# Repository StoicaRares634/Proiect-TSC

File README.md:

# Proiect-TSC
Proiect-TSC Stoica Rares-Nicolae 333CA

| Device                                                                       | CHECK_PRICES                                                                                                                                                     |
|------------------------------------------------------------------------------|------------------------------------------------------------------------------------------------------------------------------------------------------------------|
| ESP32_WROVER_EAGLE-LTSPICE_CC0402                                            |                                                                                                                                                                  |
| RCL_CPOL-EUCT3528                                                            | https://a360.co/4iZy6AA                                                                                                                                           |
| CPH3225A                                                                     | https://www.snapeda.com/parts/CPH3225A/Seiko+Instruments/view-part/?ref=eda                                                                                       |
| BUTTON_CUSYOMV1                                                              | https://industry.panasonic.com/global/en/products/control/switch/light-touch/number/evqpuj02k                                                                     |
| ADAFRUIT_LEDCHIP-LED0603                                                     | https://www.snapeda.com/parts/KP-1608SURCK/Kingbright/view-part/?ref=search                                                                                       |
| USBLC6-2SC6Y                                                                 | https://www.snapeda.com/parts/USBLC6-2SC6Y/STMicroelectronics/view-part/?ref=eda                                                                                  |
| ESP32_WROVER_AVX---SD0805S020S1R0                                            | https://eu.mouser.com/ProductDetail/KYOCERA-AVX/SD0805S020S1R0?qs=jCA%252BPfw4LHbpkAoSnwrdjw%3D%3D                                                                |
| MBR0530                                                                      | https://www.snapeda.com/parts/MBR0530/Onsemi/view-part/?ref=eda                                                                                                   |
| PGB1010603MR                                                                 | https://www.snapeda.com/parts/PGB1010603MR/Littelfuse/view-part/?ref=eda                                                                                          |
| BD5229G-TR                                                                   | https://componentsearchengine.com/part-view/BD5229G-TR/ROHM%20Semiconductor                                                                                       |
| XC6220A331MR-G                                                               | https://componentsearchengine.com/part-view/XC6220A331MR-G/Torex                                                                                                  |
| FH34SRJ-24S-0.5SH_99_                                                        | https://componentsearchengine.com/part-view/XC6220A331MR-G/Torex                                                                                                  |
| SAMACSYS_PARTS_USB4110-GF-A                                                  | https://componentsearchengine.com/part-view/USB4110-GF-A/GCT%20(GLOBAL%20CONNECTOR%20TECHNOLOGY)                                                                  |
| 112A-TAAR-R03_ATTEND                                                         | https://store.comet.srl.ro/Catalogue/Product/43497/                                                                                                               |
| 744043680IND_4828-WE-TPC_WRE                                                 | https://eu.mouser.com/ProductDetail/Wurth-Elektronik/744043680?qs=PGXP4M47uW6VkZq%252BkzjrHA%3D%3D                                                                |
| ESP32C6_VARISTORCN1812                                                       | https://www.mouser.co.uk/ProductDetail/EPCOS-TDK/B72520T0350K062?qs=dEfas%2FXlABIszF52uu7vrg%3D%3D                                                                |
| ESP32_WROVER_SPARKFUN-DISCRETESEMI_MOSFET_PCH-DMG2305UX-7                    | https://componentsearchengine.com/part-view/DMG2305UX-7/Diodes%20Incorporated                                                                                     |
| D8                                                                           | https://componentsearchengine.com/part-view/SI1308EDL-T1-GE3/Vishay                                                                                               |
| ESP32_WROVER_EAGLE-LTSPICE_RR0402                                            | https://componentsearchengine.com/part-view/R0402%201%25%20100%20K%20(RC0402FR-07100KL)/YAGEO                                                                     |
| BME680                                                                       | https://www.snapeda.com/parts/BME680/Bosch/view-part/?welcome=home                                                                                                |
| SJ                                                                           | https://grabcad.com/library/solder-jumpers-1                                                                                                                     |
| W25Q512JVEIQ                                                                 | https://www.snapeda.com/parts/W25Q512JVEIQ/Winbond+Electronics/view-part/?ref=eda                                                                                 |
| ESP32-C6-WROOM-1-N8                                                          | https://www.snapeda.com/parts/ESP32-C6-WROOM-1-N8/Espressif+Systems/view-part/?ref=eda                                                                            |
| DS3231SN#                                                                    | https://www.snapeda.com/parts/DS3231SN%23/Analog+Devices/view-part/?ref=eda                                                                                       |
| MAX17048G+T10                                                                | https://www.snapeda.com/parts/MAX17048G+T10/Analog+Devices/view-part/?ref=eda                                                                                     |

## Descriere detaliata a functionalitatii hardware

Proiectul utilizeaza microcontroller-ul ESP32-C6 WROOM. Acesta gestioneaza comunicatia cu diverse module prin interfete SPI, I2C si GPIO, avand capacitate extinsa pentru conectivitate wireless si control de periferice.

### Structura de alimentare

- Conector USB-C: asigura alimentarea externa si transferul de date.
- Controler incarcare baterie Li-Po (MCP73831): integreaza functii de incarcare sigura si controlata a bateriei.
- Baterie Li-Po: sursa de energie mobila, folosita pentru autonomie.
- LDO Regulator (XC6206): reduce tensiunea de la baterie la 3.3V stabili, necesari ESP32 si altor componente.

### Module conectate la ESP32-C6 si interfetele lor

#### 1. Senzor ambiental BME688
- Interfata: I2C
- Functii: detecteaza temperatura, presiune, umiditate si compusi volatili (calitate aer).
- Pini ESP32-C6:
  - GPIO4 → SDA
  - GPIO5 → SCL
GPIO4 si GPIO5 sunt GPIO standard cu suport I2C hardware.

#### 2. Modul RTC – DS3231SN
- Interfata: I2C
- Functii: mentine timpul real precis, inclusiv in standby.
- Pini ESP32-C6:
  - Impartiti cu BME688: GPIO4 (SDA) si GPIO5 (SCL)

#### 3. Memorie externa NOR Flash – W25Q512JVEIQ
- Interfata: SPI
- Functii: stocare extensiva de date nevolatile (64MB).
- Pini ESP32-C6:
  - GPIO6 → CLK
  - GPIO7 → MISO
  - GPIO8 → MOSI
  - GPIO9 → CS (Flash)
Aceasta configuratie este conforma cu pinii dedicati SPI al ESP32-C6 pentru performanta maxima.

#### 4. Modul SD Card
- Interfata: SPI (partajata cu NOR Flash)
- Pini ESP32-C6:
  - GPIO10 → CS (SD Card)
Se foloseste acelasi bus SPI ca Flash-ul, dar cu CS separat pentru selectare.

#### 5. E-Paper Display
- Subcomponente:
  - Circuit de tip e-paper + selector de tip ecran
  - Header pentru display
- Interfata: SPI
- Pini ESP32-C6:
  - GPIO11 → CS (E-Paper)
  - GPIO12 → RES (Reset)
  - GPIO13 → BUSY (Stare de incarcare)
GPIO11–13 sunt configurabili si sunt utilizati pentru semnale de control specifice E-Paper.

#### 6. Butoane de control (BOOT, RESET, CHANGE)
- Interfata: GPIO
- Pini ESP32-C6:
  - GPIO0 → BOOT
  - GPIO1 → RESET
  - GPIO2 → CHANGE
- Utilitate: ofera control manual pentru operatii precum boot, test sau configurare.

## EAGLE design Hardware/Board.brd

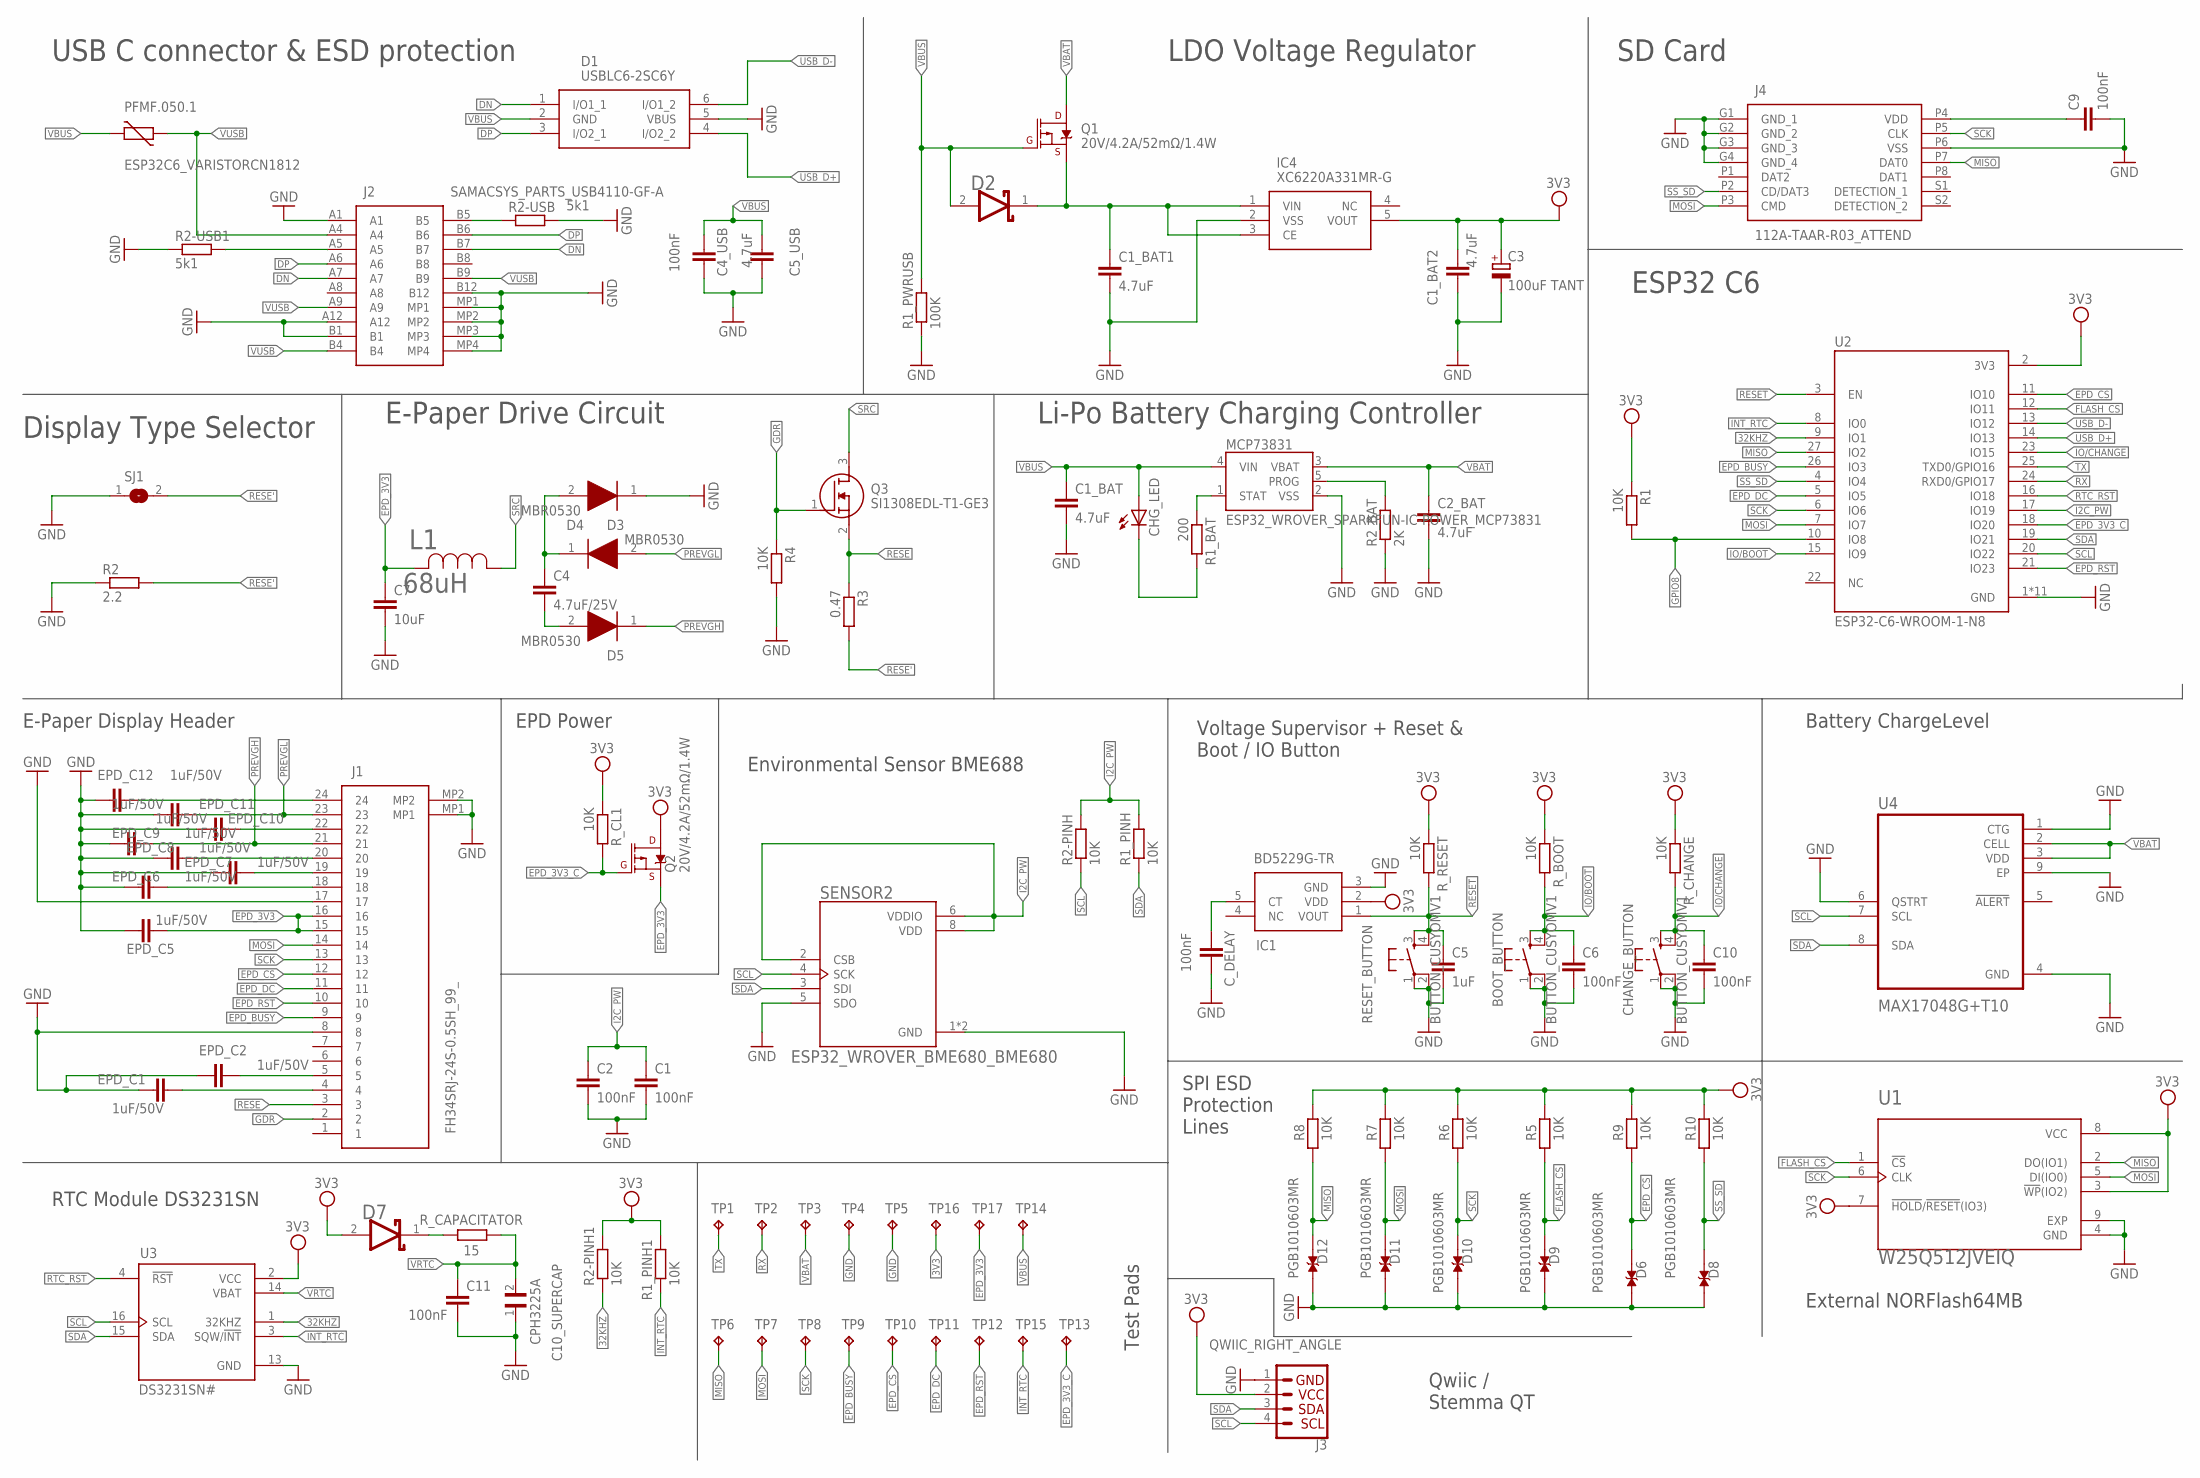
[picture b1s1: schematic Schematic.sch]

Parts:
BOOT_BUTTON: BUTTON_CUSYOMV1; MYBUTTON
C1, C2, C4_USB, C6, C10: 100nF; EAGLE-LTSPICE_C0402
C1_BAT, C1_BAT1, C5_USB: 4.7uF; EAGLE-LTSPICE_C0402
C1_BAT2, C2_BAT: 4.7uF; ESP32_WROVER_EAGLE-LTSPICE_C0402
C3: 100uF TANT; RCL_CT3528
C4: 4.7uF/25V; ESP32_WROVER_EAGLE-LTSPICE_C0402
C5: 1uF; EAGLE-LTSPICE_C0402
C7: 10uF; EAGLE-LTSPICE_C0402
C9, C11: 100nF; ESP32_WROVER_EAGLE-LTSPICE_C0402
C10_SUPERCAP: CPH3225A; CAPCP3225X100N
CHANGE_BUTTON: BUTTON_CUSYOMV1; MYBUTTON
CHG_LED: ADAFRUIT_LEDCHIP-LED0603; ADAFRUIT_CHIP-LED0603
C_DELAY: 100nF; EAGLE-LTSPICE_C0402
D1: USBLC6-2SC6Y; SOT95P280X145-6N
D2, D7: ESP32_WROVER_AVX---SD0805S020S1R0_AVX_SD0805S020S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; ESP32_WROVER_AVX---SD0805S020S1R0_AVX_SD0805S020S1R0_0
D3, D4, D5: MBR0530; SOD3716X135N
D6, D8, D9, D10, D11, D12: PGB1010603MR; DIOC1608X36N
EPD_C1, EPD_C2, EPD_C5, EPD_C6, EPD_C7, EPD_C8, EPD_C9, EPD_C10, EPD_C11, EPD_C12: 1uF/50V; EAGLE-LTSPICE_C0402
IC1: BD5229G-TR; SOT95P280X125-5N
IC4: XC6220A331MR-G; SOT95P280X120-5N
J1: FH34SRJ-24S-0.5SH_99_; FH34SRJ24S05SH99
J2: SAMACSYS_PARTS_USB4110-GF-A; SAMACSYS_PARTS_USB4110GFA
J3: QWIIC_RIGHT_ANGLE; JST04_1MM_RA
J4: 112A-TAAR-R03_ATTEND; 112ATAARR03ATTEND
L1: 68uH; IND_4828-WE-TPC_WRE
MCP73831: ESP32_WROVER_SPARKFUN-IC-POWER_MCP73831; ESP32_WROVER_SPARKFUN-IC-POWER_SOT23-5
PFMF.050.1: ESP32C6_VARISTORCN1812; ESP32C6_VARISTOR_CT/CN1812
Q1, Q2: 20V/4.2A/52mΩ/1.4W; ESP32_WROVER_SPARKFUN-DISCRETESEMI_SOT23-3
Q3: SI1308EDL-T1-GE3; SOT65P210X110-3N
R1, R1_PINH, R1_PINH1, R2-PINH, R2-PINH1, R4, R5, R6, R7, R8, R9, R10: 10K; ESP32_WROVER_EAGLE-LTSPICE_R0402
R1_BAT: 200; ESP32_WROVER_EAGLE-LTSPICE_R0402
R1_PWRUSB: 100K; ESP32_WROVER_EAGLE-LTSPICE_R0402
R2: 2.2; ESP32_WROVER_EAGLE-LTSPICE_R0402
R2-USB, R2-USB1: 5k1; ESP32_WROVER_EAGLE-LTSPICE_R0402
R2_BAT: 2K; ESP32_WROVER_EAGLE-LTSPICE_R0402
R3: 0.47; ESP32_WROVER_EAGLE-LTSPICE_R0402
RESET_BUTTON: BUTTON_CUSYOMV1; MYBUTTON
R_BOOT: 10K; ESP32_WROVER_EAGLE-LTSPICE_R0402
R_CAPACITATOR: 15; ESP32_WROVER_EAGLE-LTSPICE_R0402
R_CHANGE: 10K; ESP32_WROVER_EAGLE-LTSPICE_R0402
R_CL1: 10K; ESP32_WROVER_EAGLE-LTSPICE_R0402
R_RESET: 10K; ESP32_WROVER_EAGLE-LTSPICE_R0402
SENSOR2: ESP32_WROVER_BME680_BME680; ESP32_WROVER_BME680_PSON80P300X300X100-8N
SJ1: SJ
TP1, TP2, TP3, TP4, TP5, TP6, TP7, TP8, TP9, TP10, TP11, TP12, TP13, TP14, TP15, TP16, TP17: TPTP20R; TP20R
U1: W25Q512JVEIQ; SON127P600X800X80-9N
U2: ESP32-C6-WROOM-1-N8; XCVR_ESP32-C6-WROOM-1-N8
U3: DS3231SN#; SOIC127P1032X265-16N
U4: MAX17048G+T10; SON50P200X200X80-9N

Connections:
3V3: C1_BAT2.1, C3.+, D7.2 (ANODE), IC1.2 (VDD), IC4.5 (VOUT), J3.2, Q2.3 (D), R1.1, R1_PINH1.2, R2-PINH1.2, R5.2, R6.2, R7.2, R8.2, R9.2, R10.2, R_BOOT.1, R_CHANGE.1, R_CL1.1, R_RESET.1, TP16.TP, U1.3 (!WP!(IO2)), U1.7 (!HOLD!/!RESET!(IO3)), U1.8 (VCC), U2.2 (3V3), U3.2 (VCC)
32KHZ: R2-PINH1.1, U2.9 (IO1), U3.1 (32KHZ)
DN: D1.1 (I/O1_1), J2.A7, J2.B7
DP: D1.3 (I/O2_1), J2.A6, J2.B6
EPD_3V3: C7.1, EPD_C5.1, J1.15, J1.16, L1.2, Q2.2 (S), TP17.TP
EPD_3V3_C: Q2.1 (G), R_CL1.2, TP13.TP, U2.18 (IO20)
EPD_BUSY: J1.9, TP9.TP, U2.26 (IO3)
EPD_CS: D6.2, J1.12, R9.1, TP10.TP, U2.11 (IO10)
EPD_DC: J1.11, TP11.TP, U2.5 (IO5)
EPD_RST: J1.10, TP12.TP, U2.21 (IO23)
FLASH_CS: D9.2, R5.1, U1.1 (!CS), U2.12 (IO11)
GDR: J1.2, Q3.1 (G), R4.1
GND: BOOT_BUTTON.1, BOOT_BUTTON.2, C1.2, C1_BAT.2, C1_BAT1.2, C1_BAT2.2, C2.2, C2_BAT.2, C3.-, C4_USB.2, C5.2, C5_USB.2, C6.2, C7.2, C9.2, C10.2, C10_SUPERCAP.1, C11.2, CHANGE_BUTTON.1, CHANGE_BUTTON.2, C_DELAY.2, D1.5 (VBUS), D3.1 (K), D6.1, D8.1, D9.1, D10.1, D11.1, D12.1, EPD_C1.2, EPD_C2.2, EPD_C5.2, EPD_C6.2, EPD_C7.2, EPD_C8.2, EPD_C9.2, EPD_C10.2, EPD_C11.2, EPD_C12.2, IC1.3 (GND), IC4.2 (VSS), J1.8, J1.17, J1.MP1, J1.MP2, J2.A1, J2.A12, J2.B1, J2.B12, J2.MP1, J2.MP2, J2.MP3, J2.MP4, J3.1, J4.G1 (GND_1), J4.G2 (GND_2), J4.G3 (GND_3), J4.G4 (GND_4), J4.P6 (VSS), MCP73831.2 (VSS), R1_PWRUSB.1, R2.1, R2-USB.2, R2-USB1.1, R2_BAT.1, R4.2, RESET_BUTTON.1, RESET_BUTTON.2, SENSOR2.1 (GND), SENSOR2.5 (SDO), SENSOR2.7 (GND), SJ1.1, TP4.TP, TP5.TP, U1.4 (GND), U1.9 (EXP), U2.1 (GND), U2.28 (GND), U2.29_1 (GND), U2.29_2 (GND), U2.29_3 (GND), U2.29_4 (GND), U2.29_5 (GND), U2.29_6 (GND), U2.29_7 (GND), U2.29_8 (GND), U2.29_9 (GND), U3.13 (GND), U4.1 (CTG), U4.4 (GND), U4.6 (QSTRT), U4.9 (EP)
GPIO8: R1.2, U2.10 (IO8)
I2C_PW: C1.1, C2.1, R1_PINH.2, R2-PINH.2, SENSOR2.2 (CSB), SENSOR2.6 (VDDIO), SENSOR2.8 (VDD), U2.17 (IO19)
INT_RTC: R1_PINH1.1, TP15.TP, U2.8 (IO0), U3.3 (SQW/!INT)
IO/BOOT: BOOT_BUTTON.3, BOOT_BUTTON.4, C6.1, R_BOOT.2, U2.15 (IO9)
IO/CHANGE: C10.1, CHANGE_BUTTON.3, CHANGE_BUTTON.4, R_CHANGE.2, U2.23 (IO15)
MISO: D12.2, J4.P7 (DAT0), R8.1, TP6.TP, U1.2 (DO(IO1)), U2.27 (IO2)
MOSI: D11.2, J1.14, J4.P3 (CMD), R7.1, TP7.TP, U1.5 (DI(IO0)), U2.7 (IO7)
unnamed: C9.1, J4.P4 (VDD)
unnamed: J2.A5, R2-USB1.2
unnamed: J2.B5, R2-USB.1
unnamed: C4.2, D5.2 (A)
unnamed: C4.1, D3.2 (A), D4.1 (K)
unnamed: C1_BAT1.1, D2.1 (CATHODE), IC4.1 (VIN), IC4.3 (CE), Q1.2 (S)
unnamed: MCP73831.1 (STAT), R1_BAT.1
unnamed: CHG_LED.C, R1_BAT.2
unnamed: C_DELAY.1, IC1.5 (CT)
unnamed: MCP73831.5 (PROG), R2_BAT.2
unnamed: EPD_C12.1, J1.24
unnamed: EPD_C2.1, J1.5
unnamed: EPD_C1.1, J1.4
unnamed: EPD_C10.1, J1.22
unnamed: D7.1 (CATHODE), R_CAPACITATOR.2
unnamed: EPD_C8.1, J1.20
unnamed: EPD_C7.1, J1.19
unnamed: EPD_C6.1, J1.18
PREVGH: D5.1 (K), EPD_C9.1, J1.21
PREVGL: D4.2 (A), EPD_C11.1, J1.23
RESE: J1.3, Q3.2 (S), R3.1
RESE': R2.2, R3.2, SJ1.2
RESET: C5.1, IC1.1 (VOUT), RESET_BUTTON.3, RESET_BUTTON.4, R_RESET.2, U2.3 (EN)
RTC_RST: U2.16 (IO18), U3.4 (!RST)
RX: TP2.TP, U2.24 (RXD0/GPIO17)
SCK: D10.2, J1.13, J4.P5 (CLK), R6.1, TP8.TP, U1.6 (CLK), U2.6 (IO6)
SCL: J3.4, R2-PINH.1, SENSOR2.4 (SCK), U2.20 (IO22), U3.16 (SCL), U4.7 (SCL)
SDA: J3.3, R1_PINH.1, SENSOR2.3 (SDI), U2.19 (IO21), U3.15 (SDA), U4.8 (SDA)
SRC: L1.1, Q3.3 (D)
SS_SD: D8.2, J4.P2 (CD/DAT3), R10.1, U2.4 (IO4)
TX: TP1.TP, U2.25 (TXD0/GPIO16)
USB_D+: D1.4 (I/O2_2), U2.14 (IO13)
USB_D-: D1.6 (I/O1_2), U2.13 (IO12)
VBAT: C2_BAT.1, MCP73831.3 (VBAT), Q1.3 (D), TP3.TP, U4.2 (CELL), U4.3 (VDD)
VBUS: C1_BAT.1, C4_USB.1, C5_USB.1, CHG_LED.A, D1.2 (GND), D2.2 (ANODE), MCP73831.4 (VIN), PFMF.050.1.2, Q1.1 (G), R1_PWRUSB.2, TP14.TP
VRTC: C10_SUPERCAP.2, C11.1, R_CAPACITATOR.1, U3.14 (VBAT)
VUSB: J2.A4, J2.A9, J2.B4, J2.B9, PFMF.050.1.1

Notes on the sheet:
USB C connector & ESD protection
LDO Voltage Regulator
SD Card
Display Type Selector
E-Paper Drive Circuit
Li-Po Battery Charging Controller
ESP32 C6
E-Paper Display Header
EPD Power
Environmental Sensor BME688
Voltage Supervisor + Reset & Boot / IO Button
Battery ChargeLevel
RTC Module DS3231SN
Test Pads
Qwiic / Stemma QT
SPI ESD Protection Lines
External NORFlash64MB

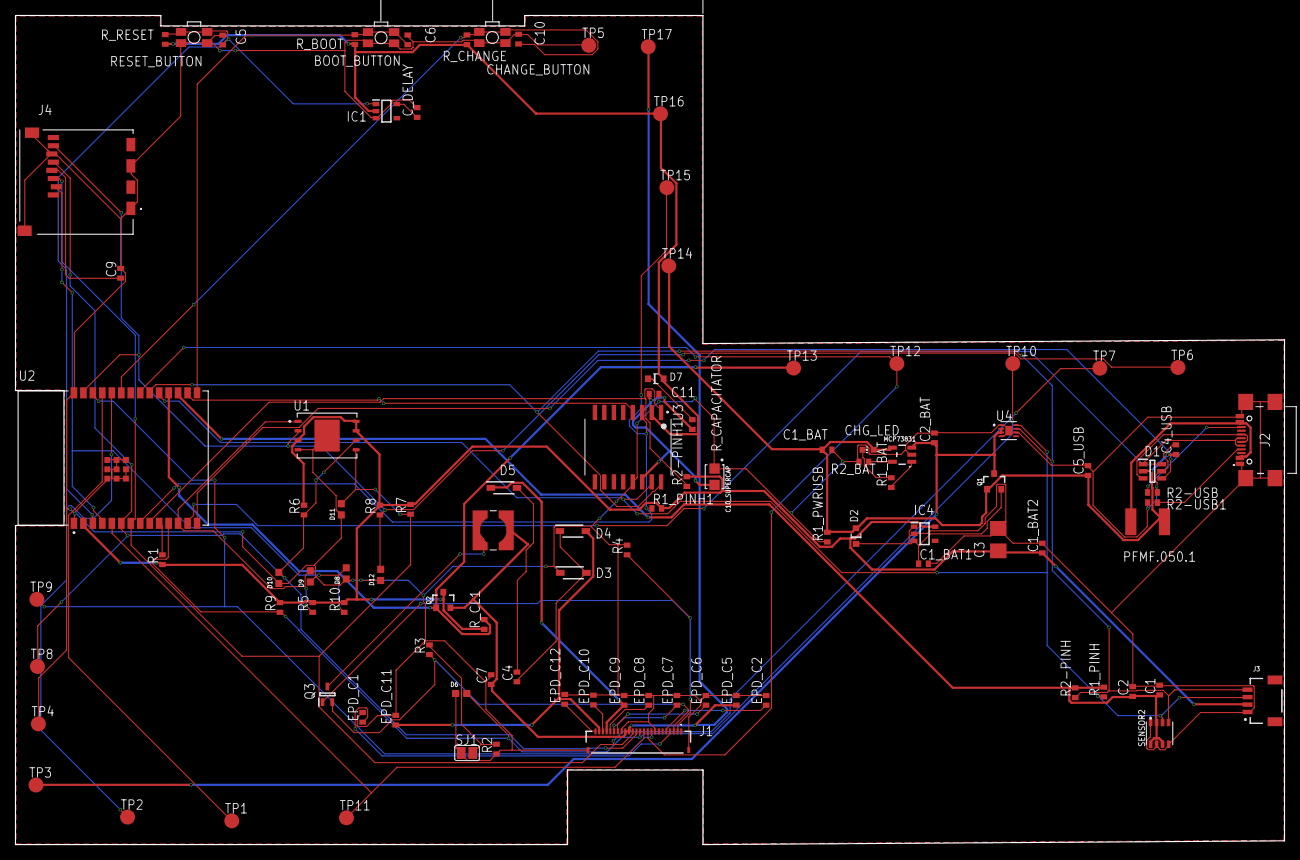
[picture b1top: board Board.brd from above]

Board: 2 copper layers, 170.2 x 111.2 mm, 103 parts (0 on the bottom side), 57 nets.

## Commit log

2025-04-06 Create LICENSE
2025-04-06 Add files via upload
    imi zice ca e prea mare, daca pun direct file-ul

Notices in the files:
parts and their libraries:
COPYRIGHT: Copyright (C) 2024 Ultra Librarian. All rights reserved.
